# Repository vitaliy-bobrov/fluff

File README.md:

# Fluff

The repository contains KiCad source files: schematic, PCB, BOM.

## Schematic

## PCB (3D preview)

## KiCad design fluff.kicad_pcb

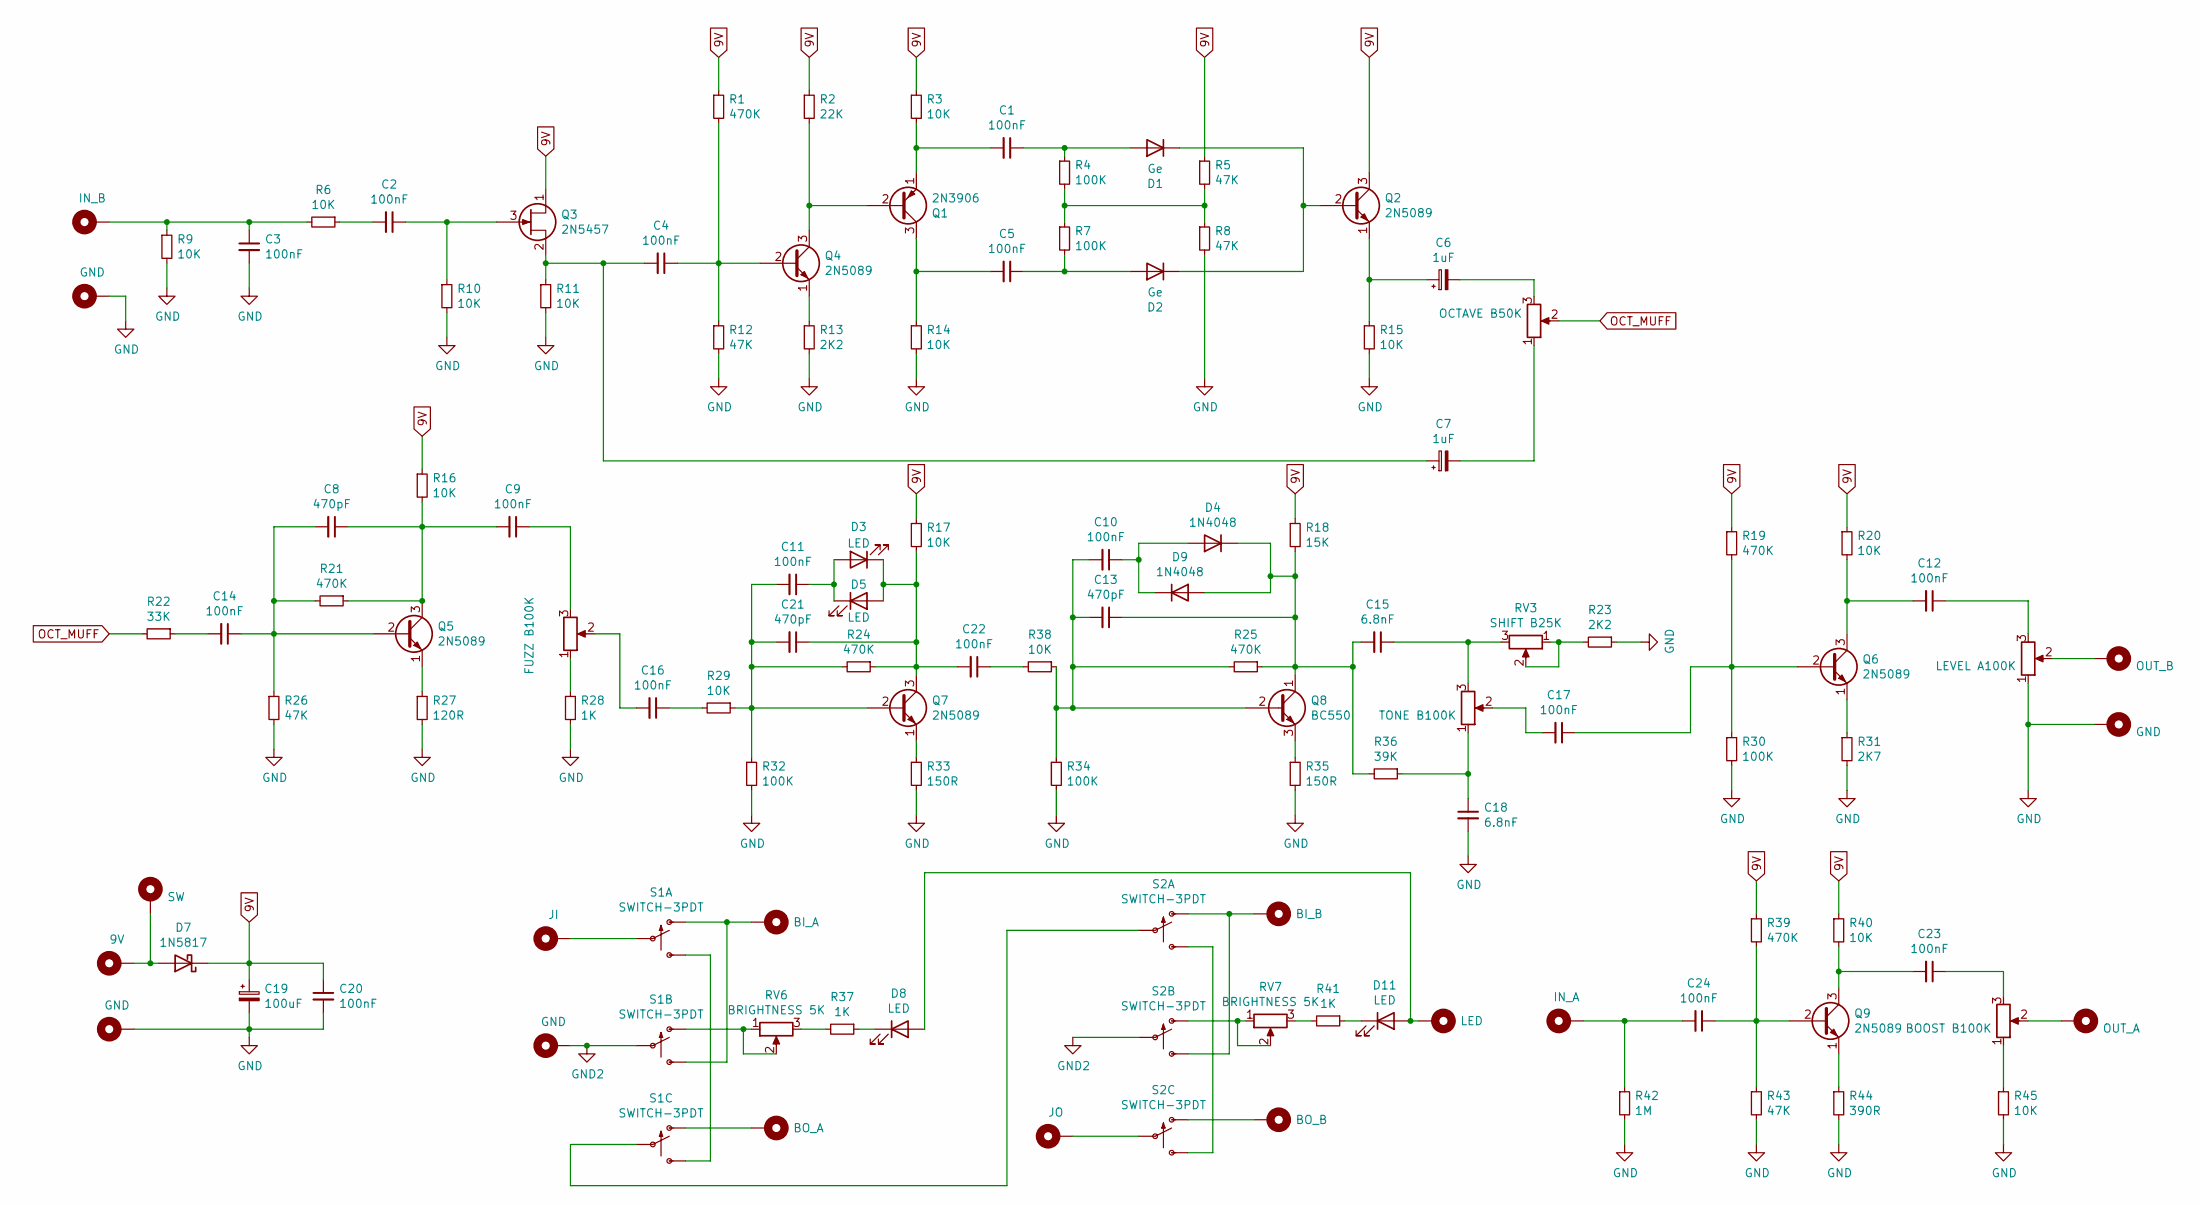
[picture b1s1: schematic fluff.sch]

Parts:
C1, C2, C3, C4, C5, C9, C10, C11, C12, C14, C16, C17, C20, C22, C23, C24: 100nF; C_Rect_L7.0mm_W2.5mm_P5.00mm
C6, C7: 1uF; CP_Radial_D5.0mm_P2.50mm
C8, C13, C21: 470pF; 0.2_22.MED
C15, C18: 6.8nF; C_Rect_L7.0mm_W2.5mm_P5.00mm
C19: 100uF; C_Rect_L7.0mm_W2.5mm_P5.00mm
D1, D2: Ge; DO35-2
D3, D5: LED; 3MM_1
D4, D9: 1N4048; DO35-2
D7: 1N5817; DO41-3
D8, D11: LED; 3MM_IO
H1: IN_B; PAD1
H2, H4, H9, H11: GND; PAD1
H3: OUT_B; PAD1
H5: SW; PAD1
H6: BI_A; PAD1
H7: JI; PAD1
H8: 9V; PAD1
H10: BI_B; PAD1
H12: BO_A; PAD1
H13: LED; PAD1
H14: IN_A; PAD1
H15: OUT_A; PAD1
H16: BO_B; PAD1
H17: JO; PAD1
Q1: 2N3906; TO92
Q2, Q4, Q5, Q6, Q7, Q9: 2N5089; TO92
Q3: 2N5457; TO92
Q8: BC550; TO92
R1, R19, R21, R24, R25, R39: 470K; 0.3%22.B
R2: 22K; 0.3%22.B
R3, R6, R9, R10, R11, R14, R15, R16, R17, R20, R29, R38, R40, R45: 10K; 0.3%22.B
R4, R7, R30, R32, R34: 100K; 0.3%22.B
R5, R8, R12, R26, R43: 47K; 0.3%22.B
R13, R23: 2K2; 0.3%22.B
R18: 15K; 0.3%22.B
R22: 33K; 0.3%22.B
R27: 120R; 0.3%22.B
R28, R37, R41: 1K; 0.3%22.B
R31: 2K7; 0.3%22.B
R33, R35: 150R; 0.3%22.B
R36: 39K; 0.3%22.B
R42: 1M; 0.3%22.B
R44: 390R; 0.3%22.B
RV1: OCTAVE B50K; 16MM_B.MOUNT
RV2: FUZZ B100K; 16MM_B.MOUNT
RV3: SHIFT B25K; 16MM_B.MOUNT
RV4: LEVEL A100K; 16MM_B.MOUNT
RV5: TONE B100K; 16MM_B.MOUNT
RV6, RV7: BRIGHTNESS 5K; TRIM1
RV8: BOOST B100K; 16MM_B.MOUNT
S1, S2: SWITCH-3PDT; 3PDT.LUGS.SPF

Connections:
9V: C19.1, C20.1, D7.1 (K), Q2.3 (C), Q3.1 (D), R1.1, R2.1, R3.1, R5.1, R16.1, R17.1, R18.1, R19.1, R20.1, R39.1, R40.1
GND: C3.2, C18.2, C19.2, C20.2, H2.1, H4.1, H9.1, R8.2, R9.2, R10.2, R11.2, R12.2, R13.2, R14.2, R15.2, R23.1, R26.2, R27.2, R28.2, R30.2, R31.2, R32.2, R33.2, R34.2, R35.2, R42.2, R43.2, R44.2, R45.2, RV4.1
GND2: H11.1, S1.P$5, S2.P$5
unnamed: C1.1, D1.2 (A), R4.1
unnamed: C1.2, Q1.1 (E), R3.2
unnamed: C2.1, Q3.3 (G), R10.1
unnamed: C2.2, R6.1
unnamed: C3.1, H1.1, R6.2, R9.1
unnamed: C4.1, Q4.2 (B), R1.2, R12.1
unnamed: C4.2, C7.1, Q3.2 (S), R11.1
unnamed: C5.1, D2.2 (A), R7.2
unnamed: C5.2, Q1.3 (C), R14.1
unnamed: C6.1, Q2.1 (E), R15.1
unnamed: C6.2, RV1.3
unnamed: C7.2, RV1.1
unnamed: C8.1, C9.2, Q5.3 (C), R16.2, R21.1
unnamed: C9.1, RV2.3
unnamed: C10.1, D4.2 (A), D9.1 (K)
unnamed: C10.2, C13.2, Q8.2 (B), R25.2, R34.1, R38.1
unnamed: C11.1, D3.2 (A), D5.1 (K)
unnamed: C11.2, C21.2, Q7.2 (B), R24.2, R29.1, R32.1
unnamed: C12.1, RV4.3
unnamed: C12.2, Q6.3 (C), R20.2
unnamed: C13.1, C15.2, D4.1 (K), D9.2 (A), Q8.1 (C), R18.2, R25.1, R36.2
unnamed: C8.2, C14.1, Q5.2 (B), R21.2, R26.1
unnamed: C14.2, R22.1
unnamed: C15.1, RV3.3, RV5.3
unnamed: C16.1, R29.2
unnamed: C16.2, RV2.2
unnamed: C17.1, Q6.2 (B), R19.2, R30.1
unnamed: C17.2, RV5.2
unnamed: C18.1, R36.1, RV5.1
unnamed: C21.1, C22.2, D3.1 (K), D5.2 (A), Q7.3 (C), R17.2, R24.1
unnamed: C22.1, R38.2
unnamed: C23.1, RV8.3
unnamed: C23.2, Q9.3 (C), R40.2
unnamed: C24.1, Q9.2 (B), R39.2, R43.1
unnamed: C24.2, H14.1, R42.1
unnamed: D1.1 (K), D2.1 (K), Q2.2 (B)
unnamed: D7.2 (A), H5.1, H8.1
unnamed: D8.1 (K), R37.1
unnamed: D11.1 (K), R41.1
unnamed: D8.2 (A), D11.2 (A), H13.1
unnamed: H3.1, RV4.2
unnamed: H6.1, S1.P$1 (O), S1.P$6 (S)
unnamed: H7.1, S1.P$2
unnamed: H10.1, S2.P$1 (O), S2.P$6 (S)
unnamed: H12.1, S1.P$7 (O)
unnamed: H15.1, RV8.2
unnamed: H16.1, S2.P$7 (O)
unnamed: H17.1, S2.P$8
unnamed: Q1.2 (B), Q4.3 (C), R2.2
unnamed: Q4.1 (E), R13.1
unnamed: Q5.1 (E), R27.1
unnamed: Q6.1 (E), R31.1
unnamed: Q7.1 (E), R33.1
unnamed: Q8.3 (E), R35.1
unnamed: Q9.1 (E), R44.1
unnamed: R4.2, R5.2, R7.1, R8.1
unnamed: R23.2, RV3.1, RV3.2
unnamed: R28.1, RV2.1
unnamed: R37.2, RV6.3
unnamed: R41.2, RV7.3
unnamed: R45.1, RV8.1
unnamed: RV6.1, RV6.2, S1.P$4 (O)
unnamed: RV7.1, RV7.2, S2.P$4 (O)
unnamed: S1.P$3 (S), S1.P$9 (S)
unnamed: S1.P$8, S2.P$2
unnamed: S2.P$3 (S), S2.P$9 (S)
OCT_MUFF: R22.2, RV1.2

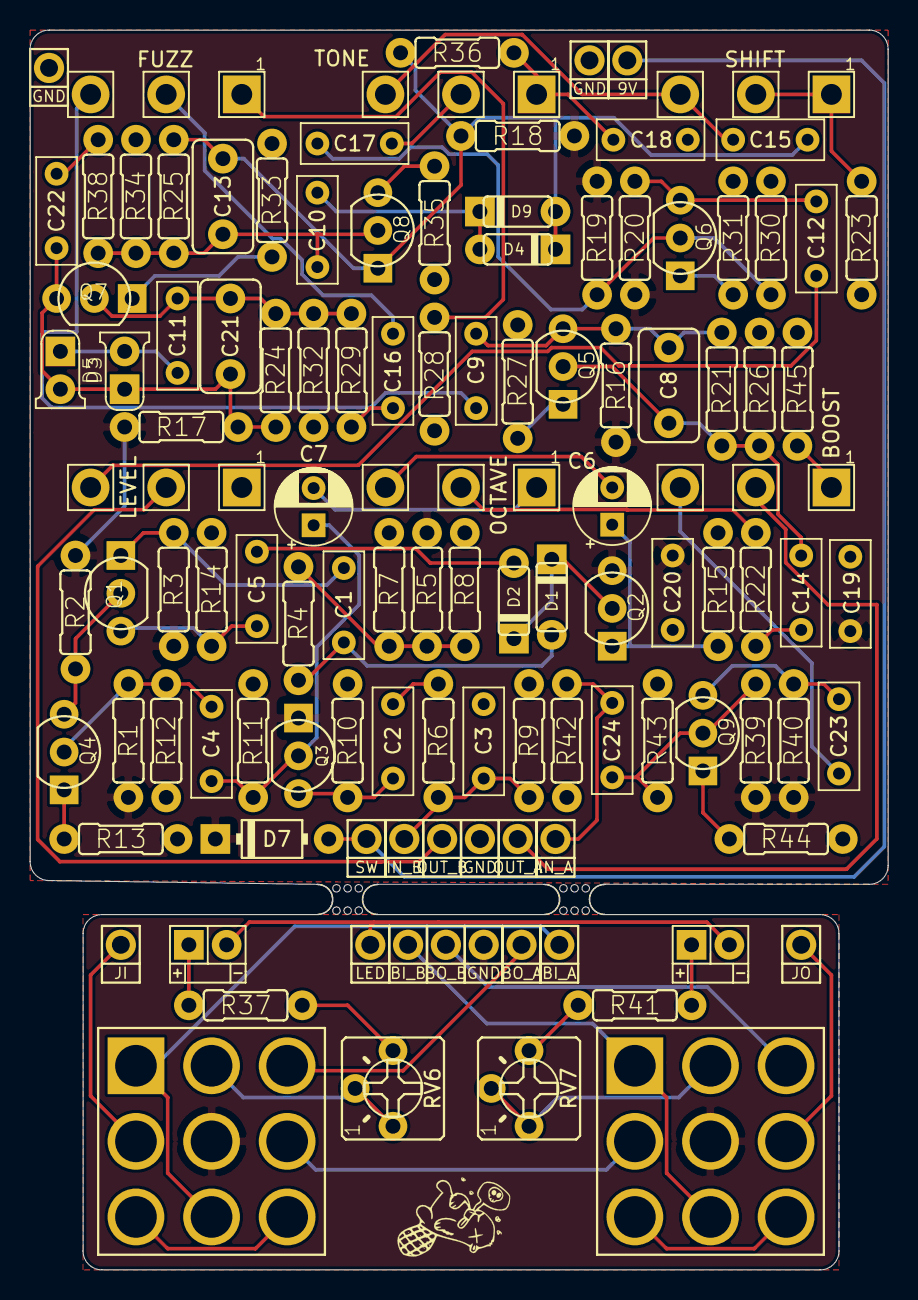
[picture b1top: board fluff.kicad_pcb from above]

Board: 2 copper layers, 57.7 x 83.3 mm, 119 parts (0 on the bottom side), 70 nets.

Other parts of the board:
JOUT4, JOUT4#2: LUMBURG_DRILL
Ref**: Val**; DC_TOP
mouse-bite-2mm-slot, mouse-bite-2mm-slot#2: VAL**; mouse-bite-2mm-slot

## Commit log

2020-12-11 v1.0
